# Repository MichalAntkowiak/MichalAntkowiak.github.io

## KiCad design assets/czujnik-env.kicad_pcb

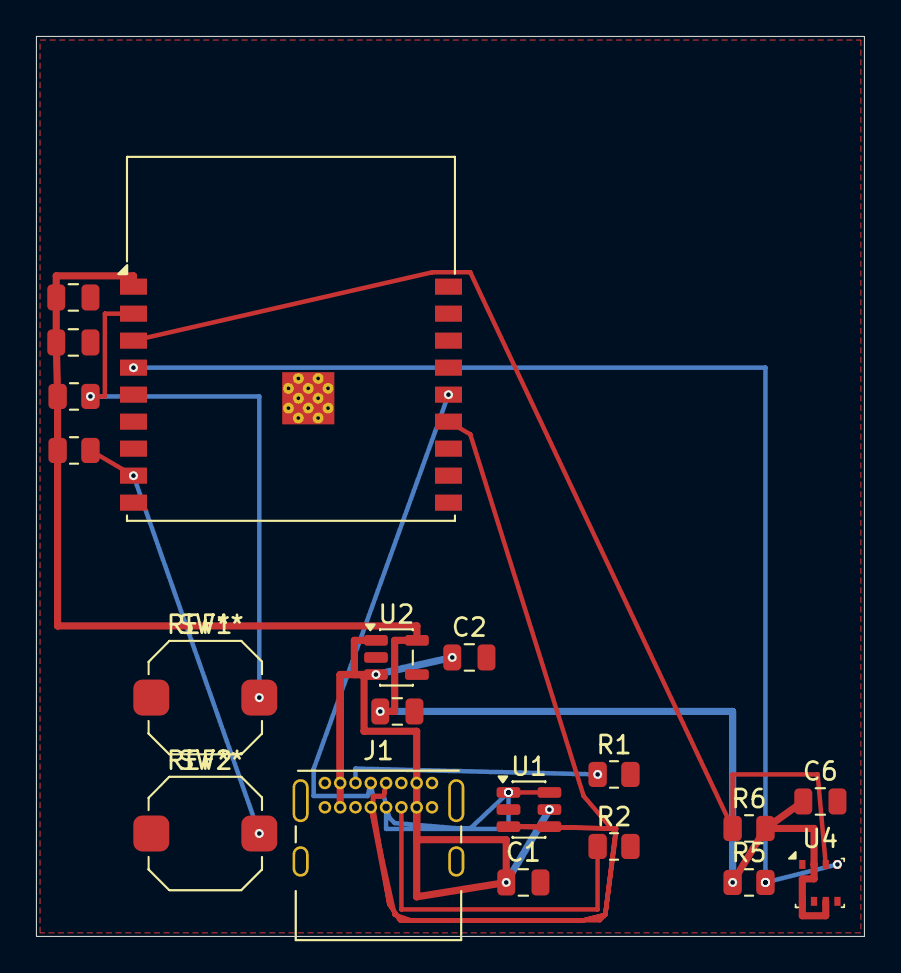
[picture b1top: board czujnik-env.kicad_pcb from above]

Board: 2 copper layers, 46.0 x 50.0 mm, 19 parts (0 on the bottom side), 11 nets.

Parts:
C1: 10 uF; C_0805_2012Metric
C2, C3: 1 uF; C_0805_2012Metric
C4: 1uF; C_0805_2012Metric
C5, C6: 100nF; C_0805_2012Metric
J1: USB_C_Receptacle_USB2.0_16P; USB_C_Receptacle_GCT_USB4085
R1, R2: 5.1k; R_0805_2012Metric
R3, R4: 10k; R_0805_2012Metric
R5, R6: 4,7k; R_0805_2012Metric
SW1, SW2: SW_Push; SW_Push_1TS009xxxx-xxxx-xxxx_6x6x5mm
U1: USBLC6-2SC6; SOT-23-6
U2: AP2112K-3.3; SOT-23-5
U3: ESP32-C3-WROOM-02
U4: BME280; Bosch_LGA-8_2.5x2.5mm_P0.65mm_ClockwisePinNumbering

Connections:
/+3V3: C3.1, C4.1, C5.1, C6.1, R3.1, R4.1, R5.1, R6.2, U2.5 (VOUT), U3.1 (3V3), U4.2 (CSB), U4.6 (VDDIO), U4.8 (VDD)
/+5V: C1.1, C2.1, J1.A4 (VBUS), J1.A9 (VBUS), J1.B4 (VBUS), J1.B9 (VBUS), U1.5 (VBUS), U2.1 (VIN), U2.3 (EN)
/SCL: R5.2, U3.4 (IO5), U4.4 (SCK)
/SDA: R6.1, U3.3 (IO4), U4.3 (SDI)
/USB_DN: J1.A7 (D-), J1.B7 (D-), U1.3 (I/O2), U1.4 (I/O2), U3.13 (IO18)
/USB_DP: J1.A6 (D+), J1.B6 (D+), U1.1 (I/O1), U1.6 (I/O1), U3.14 (IO19)
GND: C1.2, C2.2, C3.2, C4.2, C5.2, C6.2, J1.A1 (GND), J1.A12 (GND), J1.B1 (GND), J1.B12 (GND), J1.S1 (SHIELD), R1.2, R2.2, SW1.1, SW2.1, U1.2 (GND), U2.2 (GND), U3.9 (GND), U3.19 (GND), U4.1 (GND), U4.5 (SDO), U4.7 (GND)
unnamed: J1.A5 (CC1), R1.1
unnamed: J1.B5 (CC2), R2.1
unnamed: R3.2, SW1.2, U3.2 (EN)
unnamed: R4.2, SW2.2, U3.8 (IO9)

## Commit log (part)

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2026-05-21 Add initial portfolio webpage in HTML
2026-05-21 pierwsze zmiany w kodzie
2026-05-22 Add files via upload
    dodanie plików z inventora
2026-05-22 Update index.html
    aktualizacja strony
2026-05-22 Add files via upload
    dodanie zdjec doniczek
2026-05-22 Add files via upload
    dodanie odpowiednich plików
2026-05-22 Update index.html
    update strony
2026-05-22 Update index.html
    upadte strony
2026-05-22 Update index.html
    zmiana strony
2026-05-23 Fix model file name in model-viewer tag
2026-05-24 Update navigation links and hero description
2026-05-24 Update content in index.html about skills and projects
